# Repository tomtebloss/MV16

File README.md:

<h1 align="center">
MV16 smt remake
</h1>

<h2 align="center">
Atari ST MV16 cartridge by Computer's Dream and released by Ubi Soft.<br>
It was included with the game B.A.T. (Bureau of Astral Troubleshooters)
</h2>

---

---

---

## Smaller then original  

I bought the original box with cartridge a while ago with the intention to reverse engineer it. The new SMT version was done around summer 2020 (peak covid time) and is more then half as long as the original. The cartridge is a 12 bit resistor ladder with a amplifier chip. Very cheap with cardboard enclosure for the cartridge. The original seem to use very specific capacitor (Polyphenylene Sulfide, Polyethylene Naphthalate?) but I don't know if that is necessary or if it actually is that type of capacitors? Common for audio circuits perhaps? I don't know if can be substituted for normal thin/thick ceramic capacitors instead? The sound is pretty terrible and noisy but better then YM on the ST I guess. Build [Microdeal Stereo Playback](https://github.com/tomtebloss/Microdeal_Stereo_Playback) if you want better sound.

---

## BOM

Bill of material (BOM is included in gerber zip as well as text files in the 'Gerbers' directory)

| Quantity | Parts    | Value                    | Package             | Device/Description                                |
| :---     | :---     | :---                     | :---                | :---                                              |
| 9        | RN1-RN9  | 4.7 kΩ<br>(1% or better) | TC164-FR-074K7L     | Array Chip Resistor. Use 1% or better if you can  |
| 1        | R1       | 10 kΩ                    | R0805               | Resistor, Carbon film                             |
| 1        | R2       | 100 kΩ                   | R0805               | Resistor, Carbon film                             |
| 2        | C1, C2   | 10 µF                    | UD-5X5,8_NICHICON   | Electrolytic Capacitor, 50V on or higher, I used EEE-FK1H100UR                          |
| 1        | C3       | 100 µF                   | UD-6,3X7,7_NICHICON | Electrolytic Capacitor, 16V or higher, EEE-1VA101XP                                     |
| 1        | C4       | 33 nF                    | E/7260-38_NP, 2416  | Film Capacitor, Polyphenylene Sulfide (PPS), <br>Metallized - Stacked, 100V              |
| 1        | C5       | 150 nF                   | E/7260-38_NP, 2416  | Film Capacitor, Polyester, Polyethylene Naphthalate (PEN), <br>Metallized - Stacked, 63V |
| 1        | D1       | 1N4148WT                 | SOD523              | Schottky barrier diode                            |
| 1        | J1       | 35RASMT2BHNTRX           | 35RASMT2BHNTRX      | 3.5mm phone jack, surface mount                   |
| 2        | IC1, IC2 | 74XX374DW                | SOIC-20W            | Octal D type transparent LATCH, edge triggered. I used HCT. LS on original|
| 1        | IC3      | LM386M                   | SOIC-08             | Low Voltage Audio Power Amplifier. I used LM386MX |

---

## Enclosure

<h1 align="center">
                
</h1>

There is no enclosure for this. If anyone makes one, please contact me so I can add it. There is two 3mm holes that has been added on the PCB that can be used for this.

---

## Links and info

I don't know if any cracked version exist of B.A.T that can be used with the cartridge. [Scumm-VM-Lite](https://github.com/agranlund/ScummST) can be used with MV16 <br>
[Built video](https://www.youtube.com/watch?v=QhzbAAYEVPo) by Gadget UK. I [demonstrated the MV16](https://www.youtube.com/watch?v=1RnMYJRYJr0) with Scumm-VM-Lite.<br>
More photos can be found in the [Pics](Pics/) folder. <br>
Datasheet for some of the components used in the new design can be found in the [Datasheet](Datasheet/) folder. <br>
[Original cartridge pics](Pics/MV16_original_PCB_pics.rar) with all the components desoldered from PCB. <br>
[Schematics](Schematics/MV16_v1.4_schematics.pdf) and [gerbers](Gerber/MV16_v1.4_gerber.zip).
Build blog can be found on [Exxos forum](https://www.exxosforum.co.uk/forum/viewtopic.php?t=3005). I do not sell these any more! <br>
Eagle v9.6.2 [board file](Gerber/MV16_v1.4.brd) and [schematics file](Gerber/MV16_v1.4.sch) is also available.

---

## Testing

HexTracker v0.849B and a couple of other mod-trackers can be used with this cartridge. [ScummVM lite](https://www.happydaze.se/scummvm-lite-atari/) (Atari) also works. 

---

PCB routing started by Daniel Guldkrans aka DoG in Eagle around may-june 2020.

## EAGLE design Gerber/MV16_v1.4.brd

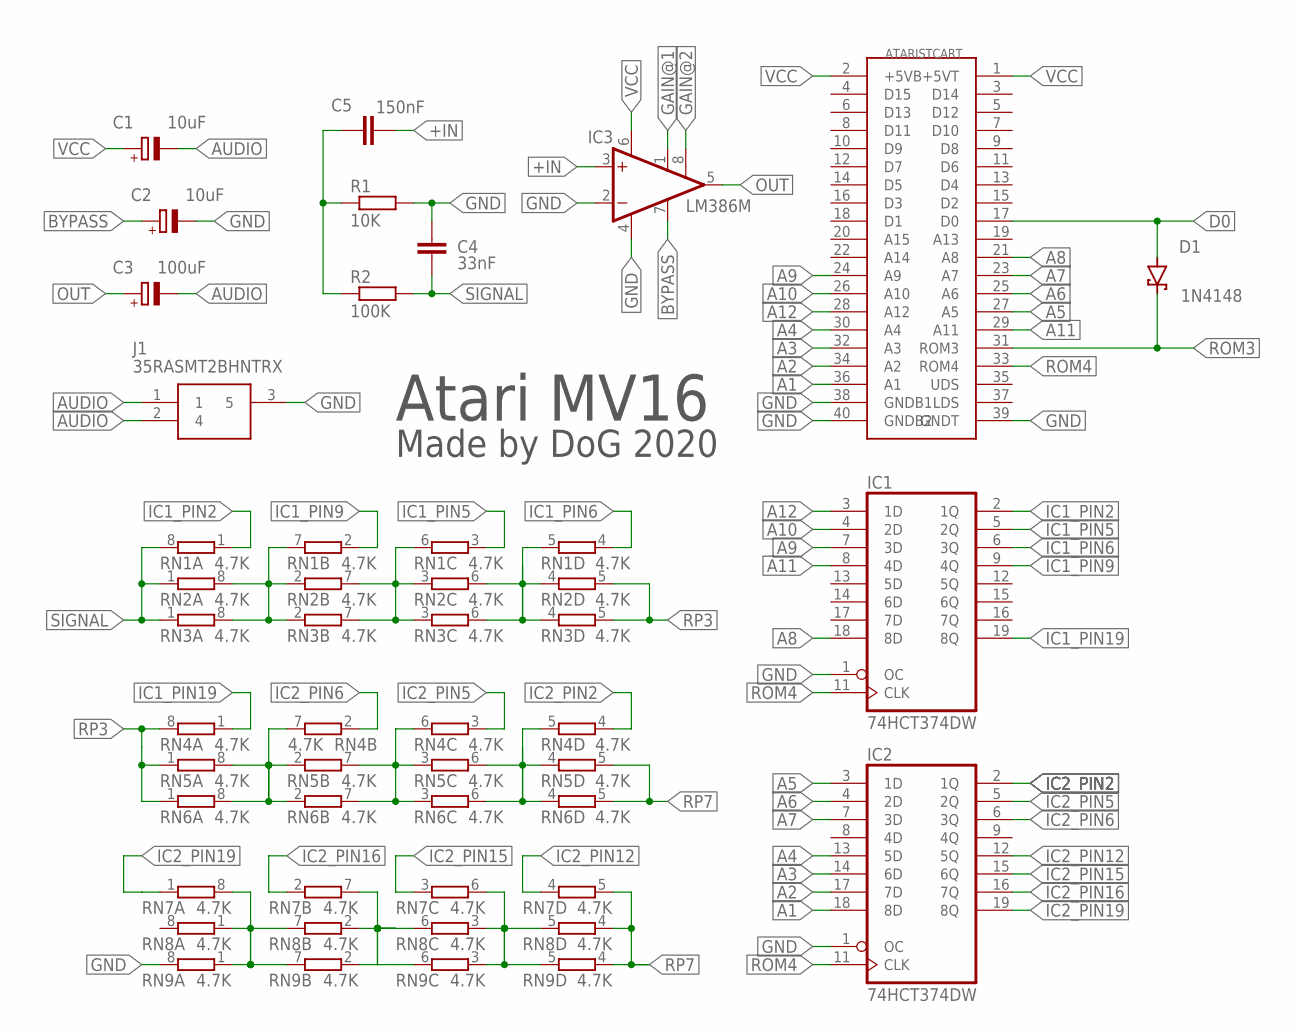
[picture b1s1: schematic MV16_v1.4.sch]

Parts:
C1, C2: 10uF; UD-5X5,8_NICHICON
C3: 100uF; UD-6,3X7,7_NICHICON
C4: 33nF; E/7260-38_NP
C5: 150nF; E/7260-38_NP
D1: 1N4148; SOD323_ST
IC1, IC2: 74HCT374DW; SO20W
IC3: LM386M; SO08
J1: 35RASMT2BHNTRX; 35RASMT2BHNTRX_1
P1: ATARI_ST_CART_FIXED; ATARI_ST_CART
R1: 10K; R0805
R2: 100K; R0805
RN1, RN2, RN3, RN4, RN5, RN6, RN7, RN8, RN9: 4.7K; EXBV8V

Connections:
+IN: C5.- (2), IC3.3 (+IN)
A1: IC2.18 (8D), P1.36 (A1)
A2: IC2.17 (7D), P1.34 (A2)
A3: IC2.14 (6D), P1.32 (A3)
A4: IC2.13 (5D), P1.30 (A4)
A5: IC2.3 (1D), P1.27 (A5)
A6: IC2.4 (2D), P1.25 (A6)
A7: IC2.7 (3D), P1.23 (A7)
A8: IC1.18 (8D), P1.21 (A8)
A9: IC1.7 (3D), P1.24 (A9)
A10: IC1.4 (2D), P1.26 (A10)
A11: IC1.8 (4D), P1.29 (A11)
A12: IC1.3 (1D), P1.28 (A12)
AUDIO: C1.-, C3.-, J1.1, J1.2 (4)
BYPASS: C2.+, IC3.7 (BYPASS)
D0: D1.A, P1.17 (D0)
GAIN@1: IC3.1 (GAIN)
GAIN@2: IC3.8 (GAIN)
GND: C2.-, C4.- (2), IC1.1 (OC), IC1.10 (GND), IC2.1 (OC), IC2.10 (GND), IC3.2 (-IN), IC3.4 (GND), J1.3 (5), P1.38 (GNDB1), P1.39 (GNDT), P1.40 (GNDB2), R1.2, RN9.8 (2)
IC1_PIN2: IC1.2 (1Q), RN1.1
IC1_PIN5: IC1.5 (2Q), RN1.3 (1)
IC1_PIN6: IC1.6 (3Q), RN1.4 (1)
IC1_PIN9: IC1.9 (4Q), RN1.2 (1)
IC1_PIN19: IC1.19 (8Q), RN4.1
IC2_PIN2: IC2.2 (1Q), RN4.4 (1)
IC2_PIN5: IC2.5 (2Q), RN4.3 (1)
IC2_PIN6: IC2.6 (3Q), RN4.2 (1)
IC2_PIN12: IC2.12 (5Q), RN7.4 (1)
IC2_PIN15: IC2.15 (6Q), RN7.3 (1)
IC2_PIN16: IC2.16 (7Q), RN7.2 (1)
IC2_PIN19: IC2.19 (8Q), RN7.1
unnamed: C5.+ (1), R1.1, R2.1
unnamed: RN4.7 (2), RN5.2 (1), RN5.8 (2), RN6.2 (1), RN6.8 (2)
unnamed: RN4.6 (2), RN5.3 (1), RN5.7 (2), RN6.3 (1), RN6.7 (2)
unnamed: RN4.5 (2), RN5.4 (1), RN5.6 (2), RN6.4 (1), RN6.6 (2)
unnamed: RN1.7 (2), RN2.2 (1), RN2.8 (2), RN3.2 (1), RN3.8 (2)
unnamed: RN1.6 (2), RN2.3 (1), RN2.7 (2), RN3.3 (1), RN3.7 (2)
unnamed: RN1.5 (2), RN2.4 (1), RN2.6 (2), RN3.4 (1), RN3.6 (2)
unnamed: RN7.8 (2), RN8.1, RN8.7 (2), RN9.1, RN9.7 (2)
unnamed: RN7.7 (2), RN8.2 (1), RN8.6 (2), RN9.2 (1), RN9.6 (2)
unnamed: RN7.6 (2), RN8.3 (1), RN8.5 (2), RN9.3 (1), RN9.5 (2)
OUT: C3.+, IC3.5 (OUT)
ROM3: D1.C, P1.31 (ROM3)
ROM4: IC1.11 (CLK), IC2.11 (CLK), P1.33 (ROM4)
RP3: RN2.5 (2), RN3.5 (2), RN4.8 (2), RN5.1, RN6.1
RP7: RN5.5 (2), RN6.5 (2), RN7.5 (2), RN8.4 (1), RN9.4 (1)
SIGNAL: C4.+ (1), R2.2, RN1.8 (2), RN2.1, RN3.1
VCC: C1.+, IC1.20 (VCC), IC2.20 (VCC), IC3.6 (VS), P1.1 (+5VT), P1.2 (+5VB)

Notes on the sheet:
Atari MV16
Made by DoG 2020

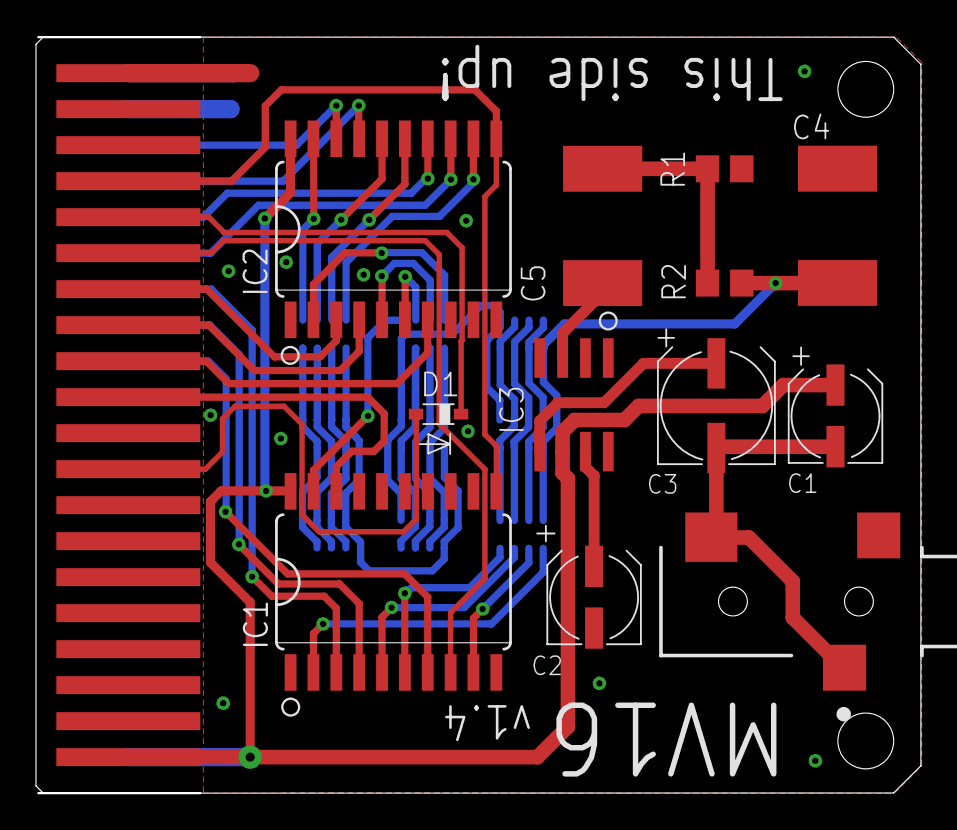
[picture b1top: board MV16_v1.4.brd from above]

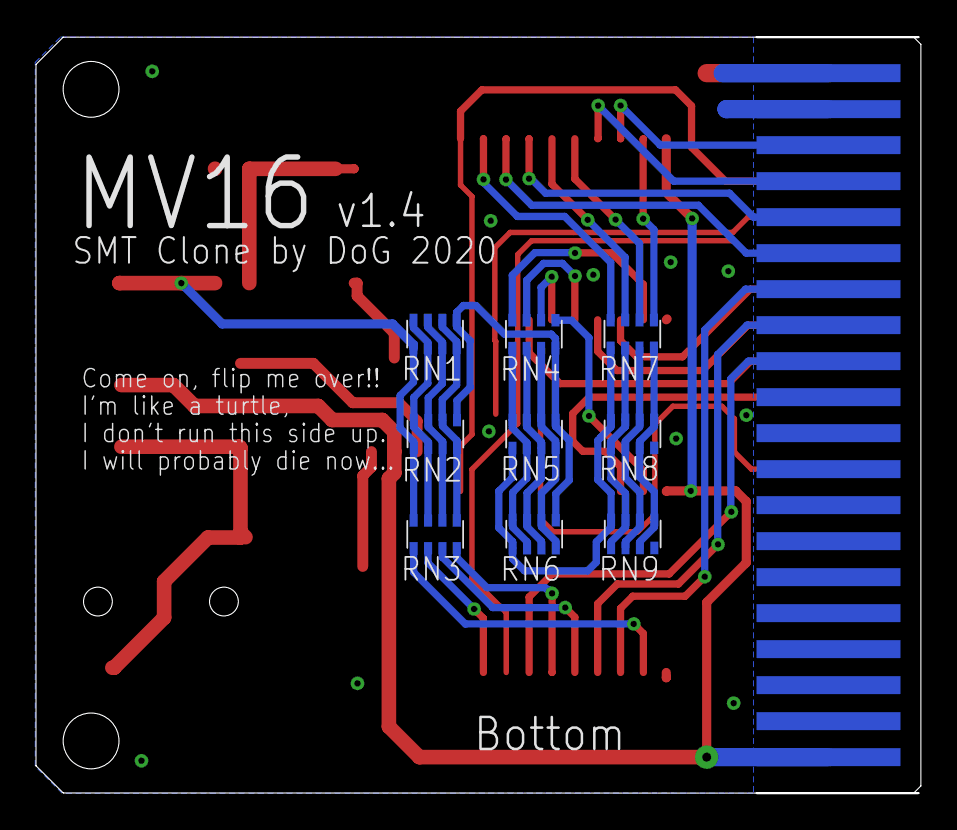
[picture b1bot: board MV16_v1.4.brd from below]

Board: 2 copper layers, 49.0 x 42.0 mm, 22 parts (9 on the bottom side), 46 nets.

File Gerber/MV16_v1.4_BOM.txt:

MV16 v1.4 BOM

Qty Value               Device              Package             Parts                                       Description                                    ALLIED_NUMBER ALLIED_PRICE-STOCK                                              DESCRIPTION                     HEIGHT MANUFACTURER_NAME MANUFACTURER_PART_NUMBER MF MOUSER_PART_NUMBER MOUSER_PRICE-STOCK                                                                                MPN OC_FARNELL OC_NEWARK POPULARITY RS_PART_NUMBER RS_PRICE-STOCK SPICEPREFIX
1   0.033uF             CPOL-USE/7260-38R   E/7260-38R          C4                                          POLARIZED CAPACITOR, American symbol                                                                                                                                                                                                                                                                                                                            1                                        C          
1   0.15uF              CPOL-USE/7260-38R   E/7260-38R          C5                                          POLARIZED CAPACITOR, American symbol                                                                                                                                                                                                                                                                                                                            1                                        C          
1   100uF               CPOL-EUUD-6,3X7,7   UD-6,3X7,7_NICHICON C3                                          POLARIZED CAPACITOR, European symbol                                                                                                                                                                                                                                                                                                                            1                                        C          
2   10uF                CPOL-EUUD-5X5,8     UD-5X5,8_NICHICON   C1, C2                                      POLARIZED CAPACITOR, European symbol                                                                                                                                                                                                                                                                                                                            0                                        C          
1   10K                 R-EU_R0805          R0805               R1                                          RESISTOR, European symbol                                                                                                                                                                                                                                                                                                                                       86                                       R          
1   100K                R-EU_R0805          R0805               R2                                          RESISTOR, European symbol                                                                                                                                                                                                                                                                                                                                       86                                       R          
1   1N4148              1N4148              SOD323_ST           D1                                          Schottky barrier diode                                                                                                                                                                                                                                                                                                                                          7                                                   
1   35RASMT2BHNTRX      35RASMT2BHNTRX      35RASMT2BHNTRX_1    J1                                          3.5mm phone jack, surface mount                70930061      https://www.alliedelec.com/switchcraft-35rasmt2bhntrx/70930061/ 3.5mm phone jack, surface mount mm     Switchcraft       35RASMT2BHNTRX              502-35RASMT2BHNTRX https://www.mouser.co.uk/ProductDetail/Switchcraft/35RASMT2B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                                                                              
9   4.7K 1%             4R-NEXBV8V          EXBV8V              RN1, RN2, RN3, RN4, RN5, RN6, RN7, RN8, RN9 Array Chip Resistor                                                                                                                                                                                                                                                                                                                        unknown    unknown   0                                                   
2   74HCT374DW          74HCT374DW          SO20W               IC1, IC2                                    Octal D type transparent LATCH, edge triggered                                                                                                                                                                                                                                                                                                                  0                                                   
1   LM386M              LM386M-1            SO08                IC3                                         Low Voltage Audio Power Amplifier                                                                                                                                                                                                                                                                                                                               0

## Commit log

2026-02-02 Gerber and BOM
2026-02-02 Top, bottom and schematics exported from EAGLE
2026-02-02 Pics of original cartridge PCB
2026-02-02 Datasheets
2026-02-02 Pics of 5 soldered MV16
2026-02-02 Pics of 9 soldered and unsoldered MV16
2026-02-11 Moved to /Schematics folder
2026-02-18 Pics from original package
2026-02-18 Update image alignment in README.md
    Changed alignment of the last image in the README.
2026-02-18 Update images in README for MV16 Cartridge and B.A.T Box
2026-02-18 Change image alignment in README.md
    Updated image alignment in README.md for better presentation.
2026-02-18 Update image alignment in README.md
    Changed alignment of the second image in README.
2026-02-18 Update MV16 cartridge image in README
    Replaced the original MV16 cartridge images with a new image.
2026-02-18 Top and bottom of original cartridge
2026-02-18 Original cartridge and with cardboard box
2026-02-18 Revise BOM format and update component details
    Updated the Bill of Materials (BOM) section to include parts and improved descriptions.
2026-02-19 Revise README with updated component details and links
    Updated details about the SMT version and components in the README.
2026-02-19 Revise README for MV16 cartridge information
    Updated project details and tips for the MV16 cartridge.
2026-02-19 New gerber with holes
2026-02-19 Revise README for clarity and grammar improvements
2026-02-19 Fix image attributes and enclosure section in README
    Updated image alignment and sizes in README.
2026-02-19 Revise capacitor entries in the components table
    Updated capacitor descriptions for clarity and formatting.
2026-02-19 EAGLE v9.6.2 files
2026-02-19 Fix wording in BOM section of README
2026-02-19 Add Eagle board and schematics file links
    Added links to Eagle board and schematics files.
2026-02-19 Fix formatting in README.md
2026-02-20 Fix formatting in README links section
2026-02-20 Clarify existence of cracked version of B.A.T
2026-02-20 Update mod-trackers information in README
2026-03-24 Fix formatting in README.md section about SMT version
